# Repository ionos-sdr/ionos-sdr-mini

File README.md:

# Ionos SDR mini

Simplified, low-cost sibling of [Ionos SDR](https://github.com/ionos-sdr/ionos-sdr): a carrier PCB that turns a stock Silicon Labs radio board into a usable SDR. An ESP32-S3 DevKitC sits on female headers on the left, a Silicon Labs radio board plugs into the mezzanine socket on the right, and both displays are optional. No custom RF design, no exotic parts — the radio board you already have in a drawer does the RF.

*rev-B3, the 2-layer variant (signals on F.Cu and B.Cu, GND poured on both sides and stitched). KiCad 10 ray-traced render: DevKitC on headers, SSD1306 OLED with BACK/OK below it, the optional ER-TFTM024-3 TFT on a 2x20 socket in the middle (manufacturer's 3D model), cursor keys and the radio board connectors on the right. The render shows the shrouded Samtec TFC model; the JLC build uses the unshrouded TFM-120-02-L-D-K-TR on the same footprint.*

**Status: rev-B3 2L built and under test — ≈ 119 hours of measurements so far** ([report](docs/ionos-mini-measurements-2026-11.md)). The firmware lives in the [main repository](https://github.com/ionos-sdr/ionos-sdr); this repo holds the carrier board, its documentation and its measurements.

## What it is

- **Carrier only.** 168 x 80 mm, four M3 nylon standoffs. Two variants: 4-layer (`layout/rev-b3`, JLC04161H-7628: F.Cu GND / In1 signal / In2 GND + power / B.Cu signal) and this 2-layer one (`layout/rev-b3-2l`, 1.6 mm FR-4, GND pour and tracks on both layers; fit R1–R5 = 82 Ω here (twin_analog on the v2 routing; 22 Ω on the 4-layer board)). No RF layout risk: matching network, SMA and shielding stay on the Silicon Labs radio board.
- **Any radio board fits.** The mezzanine pair is the standard WSTK radio board interface, so BRD4265B (FG23, 434 MHz, 10 dBm) is only the first panel. The pin-to-signal mapping differs per panel and is selected in firmware.
- **Panel auto-detect.** The radio board's M24C02 board-ID EEPROM sits on the same I2C bus as the OLED, so the firmware can read which panel is plugged in and load the matching pin map at boot.
- **Bootstrap flashing.** SWDIO, SWCLK, SWO and RESET are routed to the ESP32, which bit-bangs SWD. A blank radio board can be programmed with nothing but this board and a USB cable; routine updates then go over the UART command link. For a J-Link or Simplicity Link there is also a 1x6 2.54 mm SWD footprint (CON3) on the right edge.
- **One cable.** Power and data over the DevKit's USB-C. The radio gets its own low-noise LDO from the 5 V rail, not the DevKit's shared 3.3 V.

## Architecture

- **RX**: FG23 I/Q capture and server-side FFT lines over SPI2 (IO_MUX) to the ESP32-S3, then to the host or to the on-board display.
- **Control**: RDY handshake and a UART command link; SWD is bit-banged by the ESP32 so a blank panel can be programmed with nothing but this board.
- **Power**: a single low-noise LDO feeds VMCU_IN; the radio board's own DC-DC handles PAVDD, so one supply pin powers the whole panel.

## Hardware

| Block | Part | Notes |
| --- | --- | --- |
| MCU | ESP32-S3-DevKitC-1, N16R8 | On 2x22 female headers, antenna end overhanging the board edge |
| Radio | Silicon Labs radio board | 2x 2x20, 1.27 mm mezzanine, 24 mm apart; BRD4265B validated first |
| Display (optional) | EastRising ER-TFTM024-3, 2.4", ILI9341 | 240x320, TE pin wired for tear-free hardware scroll; resistive or capacitive touch |
| Display (optional) | SSD1306 0.96" OLED, I2C | Status line when the large display is not fitted |
| Buttons | 6+1 tactile, C&K PTS647 | UP/DOWN/LEFT/RIGHT plus BACK/OK, a seventh SPARE footprint (key optional); two resistor ladders |
| Debug (optional) | 1x6 2.54 mm SWD footprint, CON3 | Not fitted; pogo clip or solder-in pins, see below |
| Radio supply | LP5907-3.3 or TPS7A2033 | ~6.5 uVrms, fed from the DevKit 5 V rail, ferrite + 10 uF at the connector |

Seven keys cost two pins, not seven: both ladders use the same 10 k pull-up and the same 0 R / 2.2 k / 6.8 k / 22 k set to GND (UP/DOWN/LEFT/RIGHT on GPIO2, BACK/OK/SPARE on GPIO1, the 22 k level of that ladder left free), read on ADC1 with a 1 k + 100 nF filter at the pin. One threshold table serves both: 0.30 / 0.97 / 1.80 / 2.79 V. Only the 0 R keys (UP, BACK) can wake the chip from deep sleep. The freed GPIOs carry the SWD lines.

## Pin mapping (BRD4265B)

The EXP header numbers come from the Silicon Labs radio board documentation; the connector pins are what you actually route. For EXP 3 to 16 the P201 pin number equals the EXP number.

| Signal | ESP32-S3 GPIO | FG23 pin | WSTK net | Connector pin |
| --- | --- | --- | --- | --- |
| SCLK | 12 (SPI2 IO_MUX) | PC05 | WSTK_P12 | P201-15 |
| MOSI | 11 (SPI2 IO_MUX) | PC00 | WSTK_P7 | P201-10 |
| CS | 10 (SPI2 IO_MUX) | PA07 | WSTK_P10 | P201-13 |
| RDY | 14 | PD02 | WSTK_P6 | P201-9 |
| CMD | 13 (UART TX) | PA06 | WSTK_P8 | P201-11 |
| SWDIO | 38 | PA02 | WSTK_P18 | P201-21 |
| SWCLK | 39 | PA01 | WSTK_P20 | P201-23 |
| SWO | 48 | PA03 | WSTK_P16 | P201-19 |
| RESETn | 40 | RESETn | WSTK_F4 | P200-17 |
| BOARD_ID_SDA / SCL | 41 / 42 (I2C0) | - | BOARD_ID | P200-40 / P200-39 |
| VMCU_IN | - | - | VMCU_IN | P201-2 |
| 3V3 | - | - | 3V3 | P200-1 |
| GND | - | - | GND | P200-2, 38; P201-1, 39 |

The FG23 link runs on SPI2 through the IO_MUX pins so the slave interface keeps its headroom for higher clocks; the optional TFT is on SPI3. `VRF` is unused on BRD4265B and the on-board DC-DC feeds PAVDD, so a single supply pin powers the whole panel; P201-40 (VRF_IN) only runs to test point TP8, and P200-37 (5 V) has a not-fitted 0 R (R33) from the DevKit 5 V for panels that need it.

## Display and touch

The ER-TFTM024-3 sits on SPI3 (SCK 4, MOSI 5, MISO 6, CS 7, D/C 15, RST 16, BL 17, TE 18). Its resistive touch controller (XPT2046) and the module's optional SD/font/flash chips share a second header bus (pins 32/33/34), which is tied to the TFT bus on the carrier; the touch transactions run at their own ~2 MHz clock. 10 k pull-ups hold the module's SD/FONT/FLASH chip selects (header 35/36/37) inactive so nothing else drives MISO.

| Pin | Resistive (XPT2046) | Capacitive (I2C CTP) |
| --- | --- | --- |
| TCH_A, GPIO8, header 30 | SPI CS | I2C SCL |
| TCH_B, GPIO21, header 31 | PENIRQ | I2C SDA |
| TCH_INT, GPIO9, header 39 | unused | CTP INT |

Both 4.7 k pull-ups (TCH_A, TCH_B) are fitted in every build, so one BOM serves both panel types; firmware picks the mode. **Before the first power-up**, measure the panel's MISO/TE high level with VDD = 5 V: if it follows 5 V, run the panel from 3V3 or add level shifting.

## DevKit: clone or official

The carrier is laid out for the AliExpress ESP32-S3 DevKit clone, whose RGB LED is on GPIO47. On official Espressif ESP32-S3-DevKitC-1 boards the WS2812 sits on GPIO38 (v1.1) or GPIO48 (v1.0), which are SWDIO and SWO here: with an official board the LED flickers during SWD and loads the line, so remove the LED or its series resistor, or use the clone.

## SWD debug header

CON3 is a 1x6 2.54 mm row of plated holes on the right edge, outside the radio board's outline, so it stays reachable with the radio board plugged in. Pin order follows the Tag-Connect TC2030-CTX:

| Pin | 1 | 2 | 3 | 4 | 5 | 6 |
| --- | --- | --- | --- | --- | --- | --- |
| Signal | VTref (VMCU) | SWDIO | nRESET | SWCLK | GND | SWO |

The pins connect on the radio side of the solder-jumper cut points. With a debugger attached, either keep the ESP32's SWD pins as inputs in firmware or cut JP2 and JP6-JP8 to detach the ESP32 completely. VTref only senses the radio board's VMCU; the debugger must not power the board through it.

## Measurements

**Time on test so far: ≈ 119 hours** (rev-B3 2L + BRD4265B, 2–13 Nov 2026; a weekend run continues until 16 Nov):
≈ 68 h RF with a signal generator (Signal Hound VSG60), ≈ 19 h RF without a source (self-noise, residual spurs, coverage), ≈ 32 h USB-only soaks.
Raw data, scripts, logs and charts: [`measurements/ionos-mini-2026-11/`](measurements/ionos-mini-2026-11/) ([RESULT.md](measurements/ionos-mini-2026-11/RESULT.md)) · report for 2–9 Nov: [`docs/ionos-mini-measurements-2026-11.md`](docs/ionos-mini-measurements-2026-11.md) ([magyarul](docs/hu/ionos-mini-meresi-jelentes-2026-11.md)).

**Measurement types:** USB throughput and long soaks · gain, linearity and ADC clip point · noise figure and MDS · passband and image rejection · frequency accuracy and drift · tuning range (LO divider / VCO window) · lock proof with the on-board clock comb · noise floor and residual spurs (open and terminated input) · 2-FSK sensitivity and BER curves · spurious responses 30 MHz – 6 GHz · long-term stability · SoapySDR driver soak. Pending: two-tone IIP3, phase noise, TX output vs frequency.

| BRD4265B (434 MHz match) | |
|---|---|
| Receive coverage | **97 – 1562 MHz and 2025 – 3100 MHz** (no LO divider for ~1625 – 2000 MHz) |
| 434 MHz (matched) | gain 63 dB, NF 3–4 dB, MDS −133 dBm (10 dB SNR, 500 Hz), 2-FSK 5 kbps BER 10⁻² at −115 dBm, clip −62 dBm |
| 145 MHz | gain 53 dB, NF 8–9 dB, MDS −128 dBm, FSK −110 dBm, clip −53 dBm |
| 868 / 1296 MHz | NF ≈ 23 / 40 dB, FSK −93 / −73 dBm |
| 2400 / 3000 MHz | NF ≈ 55 / 46 dB, FSK −55 / −59 dBm — the 434 MHz RX match limits above ~600 MHz, the chip itself tunes and locks to 3.1 GHz |
| Spurious responses | @ 434 MHz worst −70 dBc (11 × LO), others ≤ −104 dBc, no image response; @ 868 MHz worst −81 dBc |
| I/Q over USB (TinyUSB CDC on USB‑OTG) | 200 ksps int16 (813 kB/s); 40 h: 86 M blocks, 0 device drops, 0.65 ppm host loss |
| 200 ksps bandwidth / image rejection | 88 kHz at −3 dB (PHY channel filter) / ≥ 42 dB |
| Frequency | crystal ≈ +4.2…+5.3 ppm uncorrected (temperature), corrected in firmware (`FREQ_CORR_RX_PPB`); gain stable to σ 0.02–0.03 dB below 1 GHz |
| SoapySDR | SoapyIonos works on Windows (GQRX, SoapySDRUtil, Python); every VSG run goes through it |
| Known artefact | ±6.25 kHz sidebands (−74 dBc at 5 kHz, −43 dBc at 37 kHz tone offset) from the I/Q path — open |

P_in = VSG level − 30 dB pad; the coax loss is not subtracted (matters above ~1 GHz).

## Manufacturing files

Gerbers, drill, JLCPCB BOM and CPL are attached to the GitHub release [`rev-b3-2l-jlc-20261022`](https://github.com/ionos-sdr/ionos-sdr-mini/releases/tag/rev-b3-2l-jlc-20261022), not committed. To rebuild them from the KiCad project (DRC and schematic parity must be clean, or nothing is written):

```
"C:\Program Files\KiCad\10.0\bin\python.exe" fab/jlc_pack.py
```

JLC assembles the top-side SMD parts and the two radio board connectors; the DevKit, the displays and the debug header are fitted by hand. LCSC part numbers are in `fab/jlc_lcsc.csv`.

## Repository

```
hardware/          KiCad project, fab outputs, BOM           CERN-OHL-P-2.0
docs/              pin mapping, assembly notes, renders      CC-BY-4.0
measurements/      raw data, scripts, results                CC-BY-4.0
```

Firmware lives in the [main repository](https://github.com/ionos-sdr/ionos-sdr): `firmware-fg23/` for the radio SoC, `firmware-esp32/` for the companion.

## Credits, licensing, trademarks

Hardware under CERN-OHL-P-2.0, documentation under CC-BY-4.0. Not affiliated with IONOS SE or Silicon Laboratories; EFR32, Simplicity Studio and the WSTK radio board interface are Silicon Labs property, used here for interoperability only.

Designed by Zoltán Dóczi and Zoltán Papp at [Z2 Labs](https://www.z2labs.io/), Budapest. Design and manufacturing support by [Protowoerk](https://www.protowoerk.com).

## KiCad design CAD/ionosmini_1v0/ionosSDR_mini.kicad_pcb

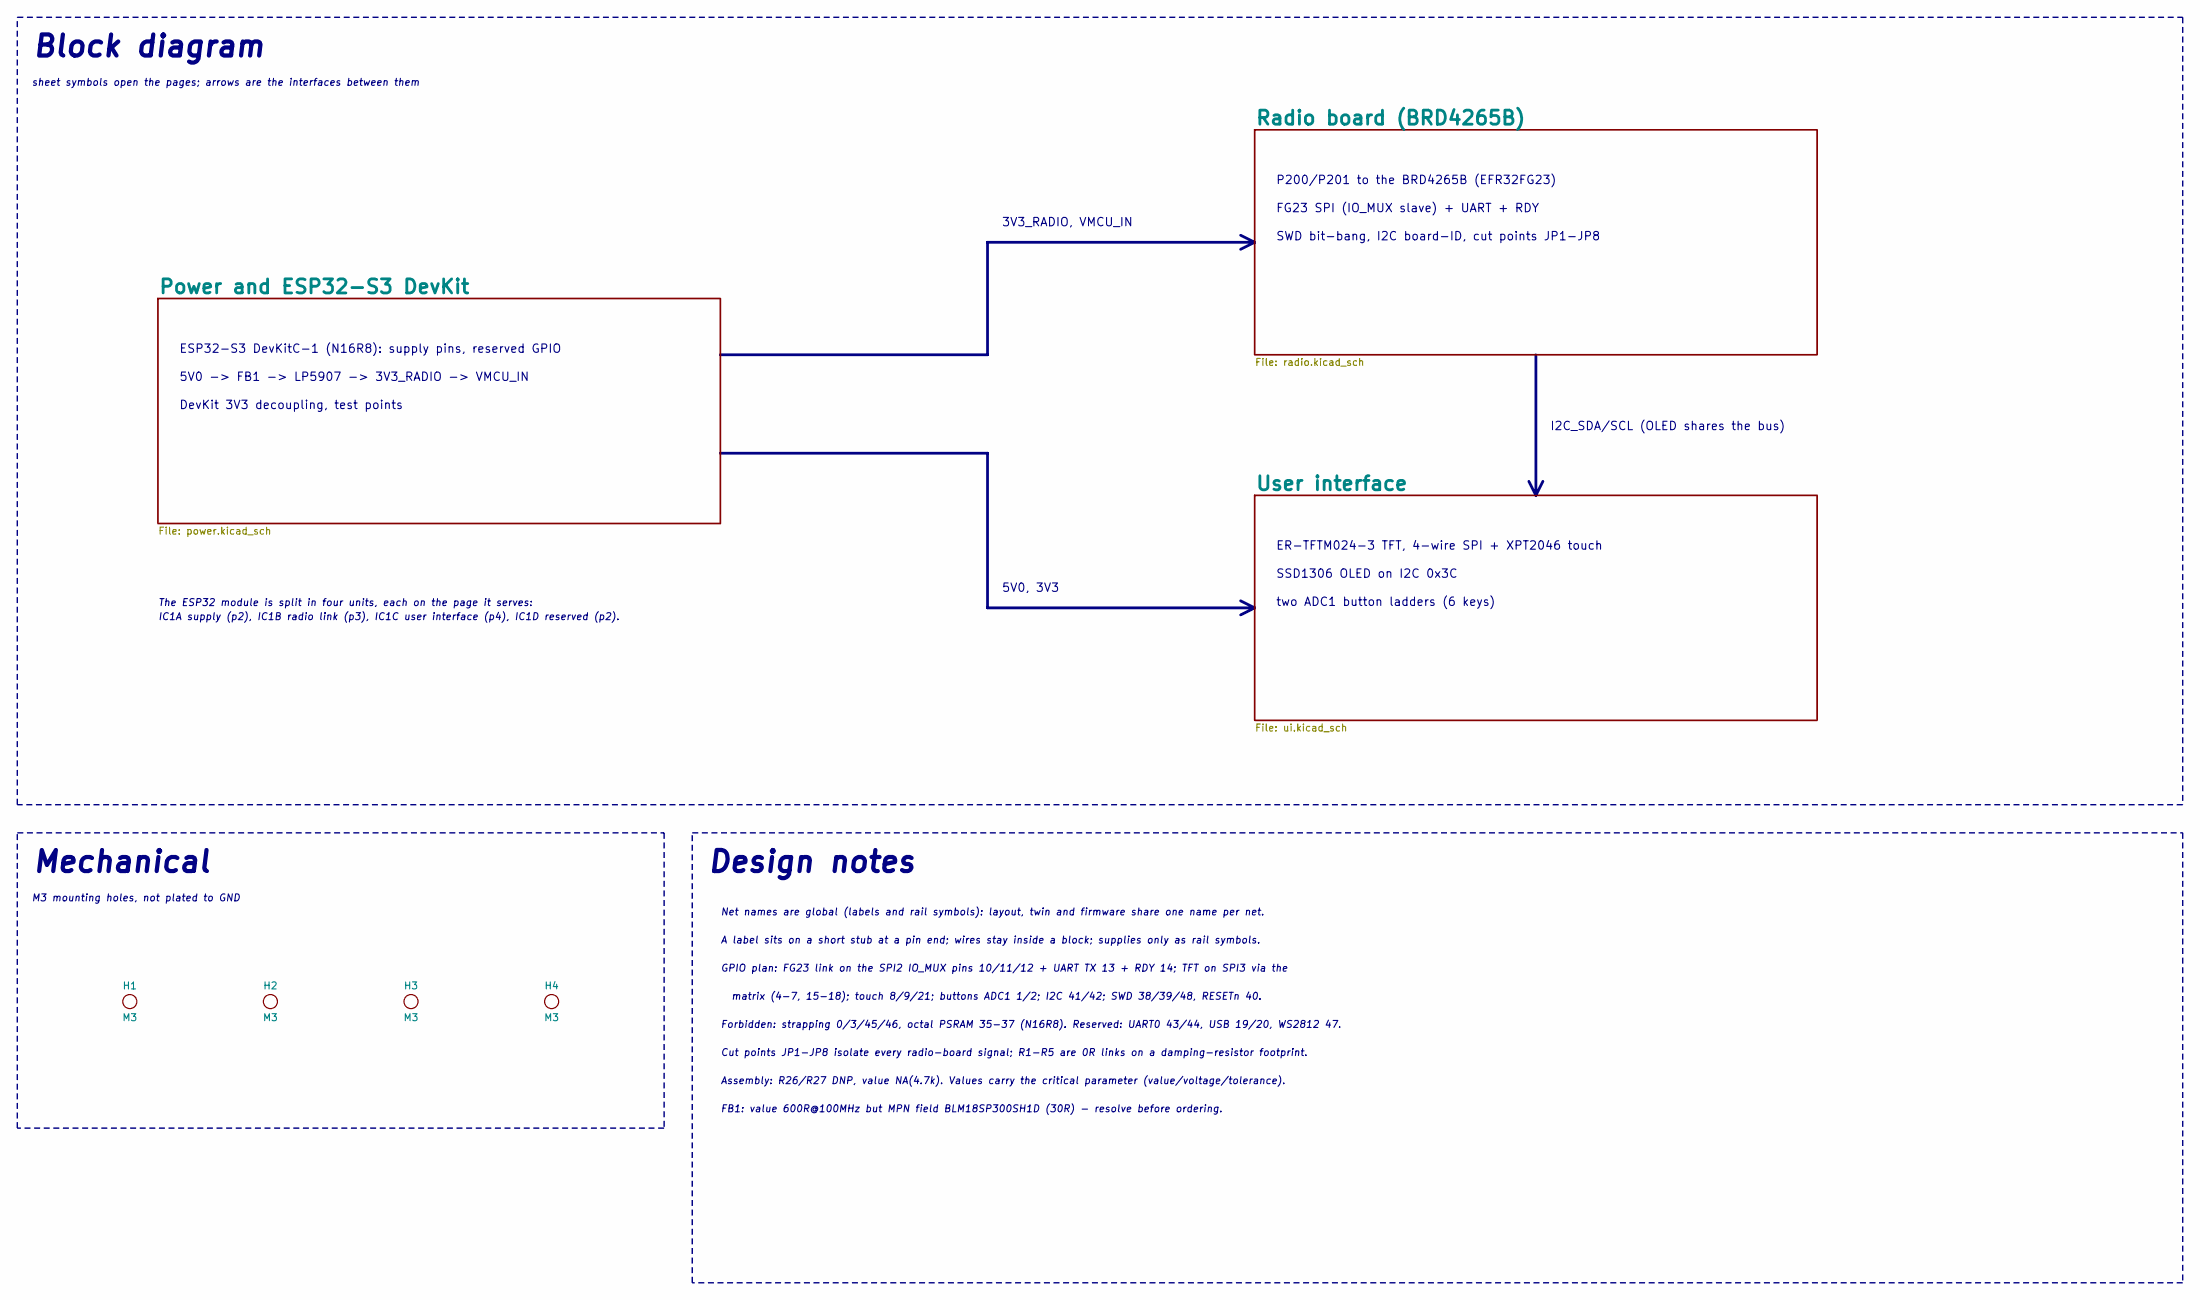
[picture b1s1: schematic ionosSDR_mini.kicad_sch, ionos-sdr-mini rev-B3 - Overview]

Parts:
H1, H2, H3, H4: M3; PB_HOLE

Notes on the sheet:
Block diagram
sheet symbols open the pages; arrows are the interfaces between them
ESP32-S3 DevKitC-1 (N16R8): supply pins, reserved GPIO
5V0 -> FB1 -> LP5907 -> 3V3_RADIO -> VMCU_IN
DevKit 3V3 decoupling, test points
P200/P201 to the BRD4265B (EFR32FG23)
FG23 SPI (IO_MUX slave) + UART + RDY
SWD bit-bang, I2C board-ID, cut points JP1-JP8
ER-TFTM024-3 TFT, 4-wire SPI + XPT2046 touch
SSD1306 OLED on I2C 0x3C
two ADC1 button ladders (6 keys)
3V3_RADIO, VMCU_IN
5V0, 3V3
I2C_SDA/SCL (OLED shares the bus)
The ESP32 module is split in four units, each on the page it serves:
IC1A supply (p2), IC1B radio link (p3), IC1C user interface (p4), IC1D reserved (p2).
Mechanical
M3 mounting holes, not plated to GND
Design notes
Net names are global (labels and rail symbols): layout, twin and firmware share one name per net.
A label sits on a short stub at a pin end; wires stay inside a block; supplies only as rail symbols.
GPIO plan: FG23 link on the SPI2 IO_MUX pins 10/11/12 + UART TX 13 + RDY 14; TFT on SPI3 via the
matrix (4-7, 15-18); touch 8/9/21; buttons ADC1 1/2; I2C 41/42; SWD 38/39/48, RESETn 40.
Forbidden: strapping 0/3/45/46, octal PSRAM 35-37 (N16R8). Reserved: UART0 43/44, USB 19/20, WS2812 47.
Cut points JP1-JP8 isolate every radio-board signal; R1-R5 are 0R links on a damping-resistor footprint.
Assembly: R26/R27 DNP, value NA(4.7k). Values carry the critical parameter (value/voltage/tolerance).
FB1: value 600R@100MHz but MPN field BLM18SP300SH1D (30R) - resolve before ordering.

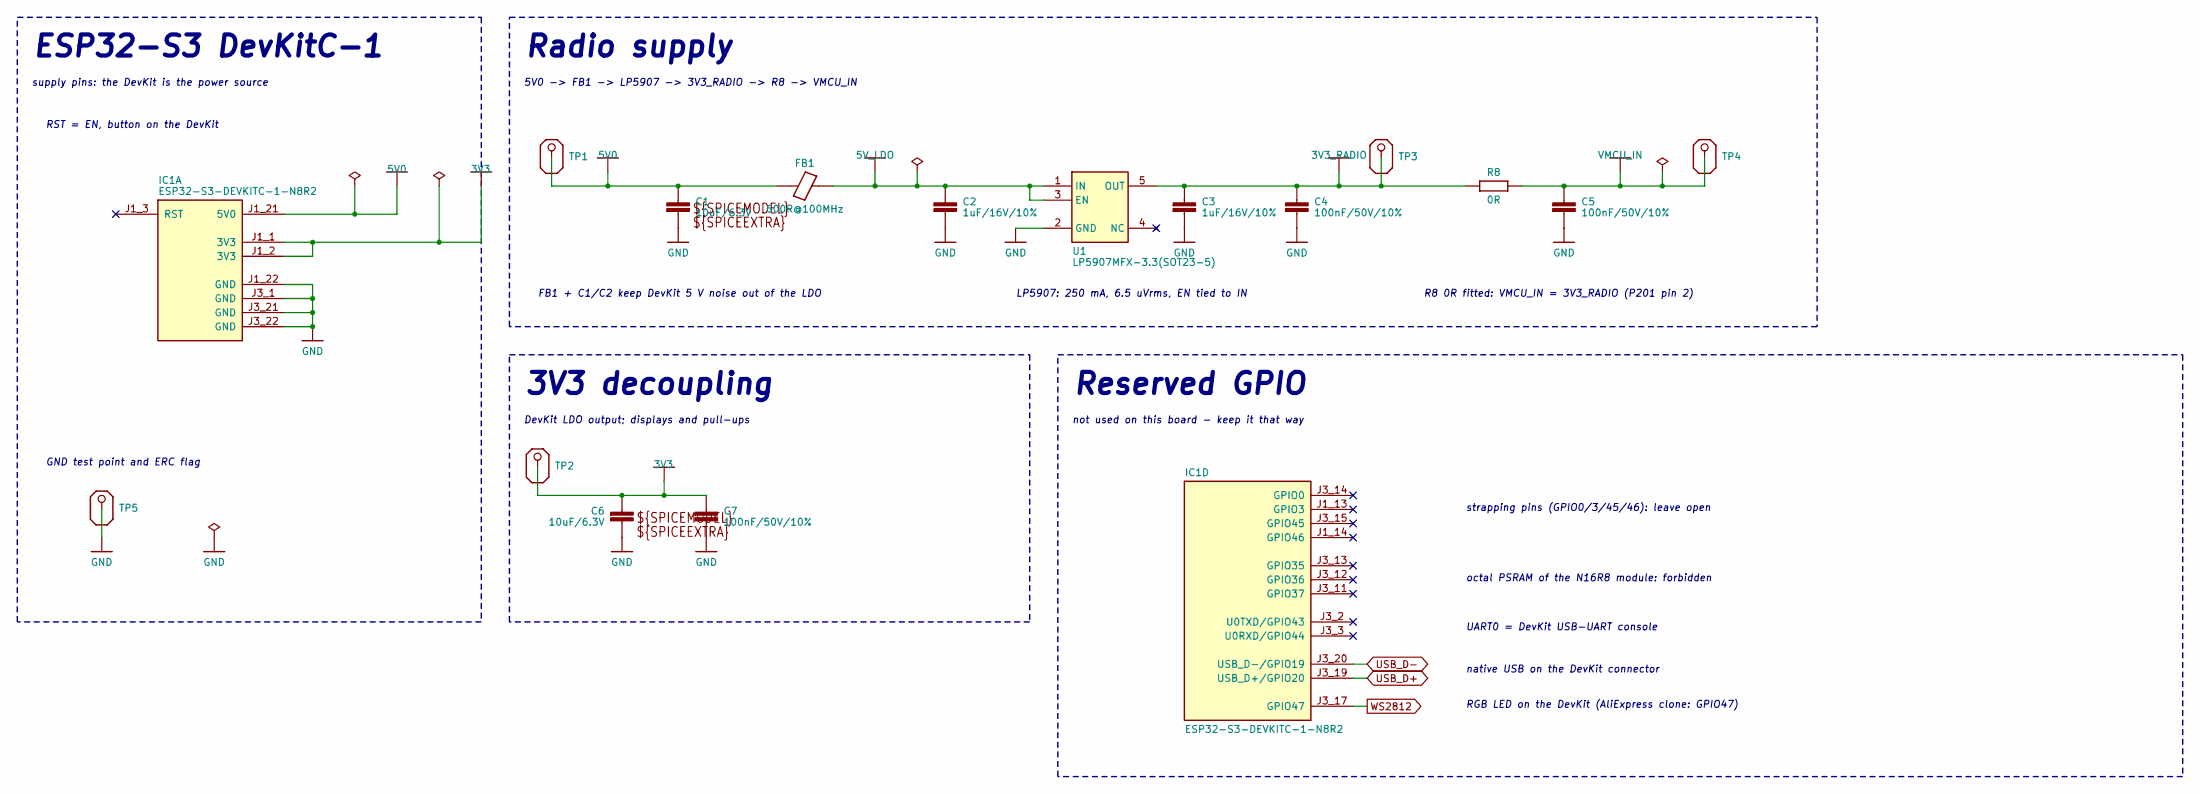
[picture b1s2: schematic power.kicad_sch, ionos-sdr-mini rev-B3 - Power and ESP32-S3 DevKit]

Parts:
C1, C6: 10uF/6.3V; CAPC1005X60_0402
C2, C3: 1uF/16V/10%; CAPC1005X60_0402; MPN CL05A105KO5NNNC
C4, C5, C7: 100nF/50V/10%; CAPC1005X60_0402; MPN GRM155R71H104KE14D
FB1: 600R@100MHz; L5_0603; MPN BLM18SP300SH1D
IC1: ESP32-S3-DEVKITC-1-N8R2; XCVR_ESP32-S3-DEVKITC-1-N8R2; MPN ESP32-S3-DEVKITC-1-N8R2
R8: 0R; RESC1005X40_0402; MPN CRCW04020000Z0EDC
TP1: 5V0; TESTPOINT_40MIL_SMD
TP2: 3V3; TESTPOINT_40MIL_SMD
TP3: 3V3_RADIO; TESTPOINT_40MIL_SMD
TP4: VMCU_IN; TESTPOINT_40MIL_SMD
TP5: GND; TESTPOINT_40MIL_SMD
U1: LP5907MFX-3.3(SOT23-5); SOT-23-5; MPN LP5907MFX-3.3/NOPB

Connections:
3V3: C6.1, C7.1, IC1.J1_1 (3V3), IC1.J1_2 (3V3), TP2.PP; also elsewhere on the board
3V3_RADIO: C3.1, C4.1, R8.1, TP3.PP, U1.5 (OUT); also elsewhere on the board
5V0: C1.1, FB1.1, IC1.J1_21 (5V0), TP1.PP; also elsewhere on the board
5V_LDO: C2.1, FB1.2, U1.1 (IN), U1.3 (EN)
GND: C1.2, C2.2, C3.2, C4.2, C5.2, C6.2, C7.2, IC1.J1_22 (GND), IC1.J3_1 (GND), IC1.J3_21 (GND), IC1.J3_22 (GND), TP5.PP, U1.2 (GND); also elsewhere on the board
USB_D+: IC1.J3_19 (USB_D+/GPIO20)
USB_D-: IC1.J3_20 (USB_D-/GPIO19)
VMCU_IN: C5.1, R8.2, TP4.PP; also elsewhere on the board
WS2812: IC1.J3_17 (GPIO47)

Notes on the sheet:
ESP32-S3 DevKitC-1
supply pins: the DevKit is the power source
GND test point and ERC flag
RST = EN, button on the DevKit
Radio supply
5V0 -> FB1 -> LP5907 -> 3V3_RADIO -> R8 -> VMCU_IN
FB1 + C1/C2 keep DevKit 5 V noise out of the LDO
LP5907: 250 mA, 6.5 uVrms, EN tied to IN
R8 0R fitted: VMCU_IN = 3V3_RADIO (P201 pin 2)
3V3 decoupling
DevKit LDO output; displays and pull-ups
Reserved GPIO
not used on this board - keep it that way
strapping pins (GPIO0/3/45/46): leave open
octal PSRAM of the N16R8 module: forbidden
UART0 = DevKit USB-UART console
native USB on the DevKit connector
RGB LED on the DevKit (AliExpress clone: GPIO47)

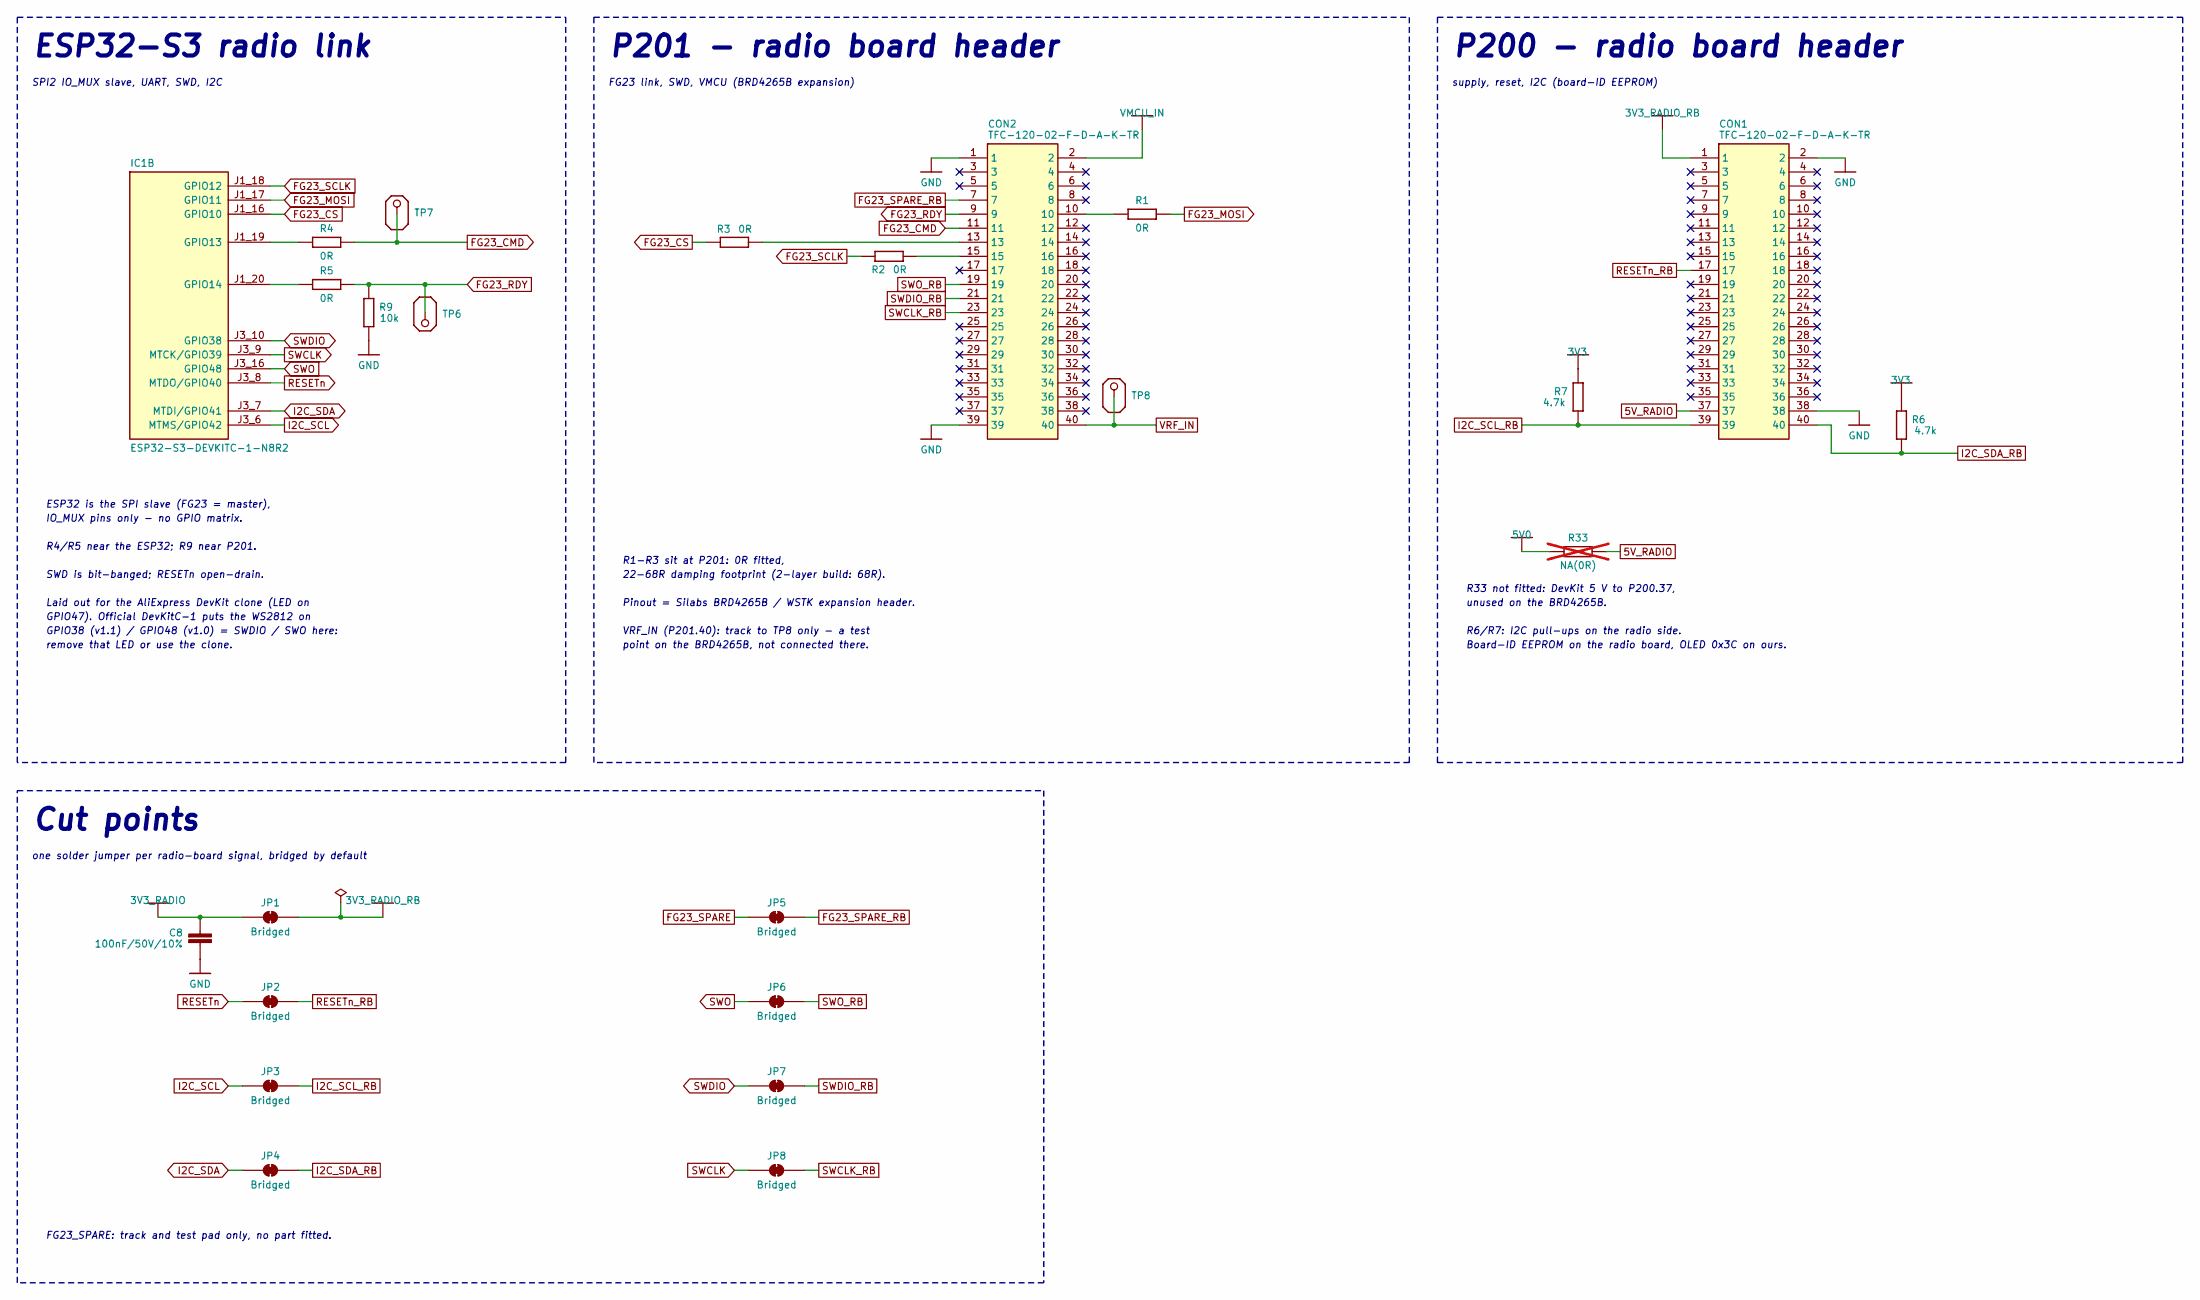
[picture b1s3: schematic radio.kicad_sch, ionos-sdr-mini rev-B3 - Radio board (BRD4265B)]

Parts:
C8: 100nF/50V/10%; CAPC1005X60_0402; MPN GRM155R71H104KE14D
CON1, CON2: TFC-120-02-F-D-A-K-TR; TFC-120-02-XX-D-A-K-TR; MPN TFC-120-02-F-D-A-K-TR
IC1: ESP32-S3-DEVKITC-1-N8R2; XCVR_ESP32-S3-DEVKITC-1-N8R2; MPN ESP32-S3-DEVKITC-1-N8R2
JP1, JP2, JP3, JP4, JP5, JP6, JP7, JP8: Bridged; SolderJumper-2_P1.3mm_Bridged_RoundedPad1.0x1.5mm
R1, R2, R3, R4, R5: 0R; RESC1005X40_0402; MPN CRCW04020000Z0EDC
R6, R7: 4.7k; RESC1005X40_0402; MPN CR0402AJW-472GAS
R9: 10k; RESC1005X40_0402; MPN CRCW040210K0FKED
R33: NA(0R); RESC1005X40_0402; MPN CRCW04020000Z0EDC; not fitted
TP6: FG23_RDY; TESTPOINT_40MIL_SMD
TP7: FG23_CMD; TESTPOINT_40MIL_SMD
TP8: VRF_IN; TESTPOINT_40MIL_SMD

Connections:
3V3: R6.2, R7.2; also elsewhere on the board
3V3_RADIO: C8.1, JP1.1 (A); also elsewhere on the board
3V3_RADIO_RB: CON1.1, JP1.2 (B)
5V0: R33.1; also elsewhere on the board
5V_RADIO: CON1.37, R33.2
FG23_CMD: CON2.11, R4.1, TP7.PP
FG23_CS: IC1.J1_16 (GPIO10), R3.1
FG23_MOSI: IC1.J1_17 (GPIO11), R1.2
FG23_RDY: CON2.9, R5.1, R9.1, TP6.PP
FG23_SCLK: IC1.J1_18 (GPIO12), R2.1
FG23_SPARE: JP5.1 (A)
FG23_SPARE_RB: CON2.7, JP5.2 (B)
GND: C8.2, CON1.2, CON1.38, CON2.1, CON2.39, R9.2; also elsewhere on the board
I2C_SCL: IC1.J3_6 (MTMS/GPIO42), JP3.1 (A); also elsewhere on the board
I2C_SCL_RB: CON1.39, JP3.2 (B), R7.1
I2C_SDA: IC1.J3_7 (MTDI/GPIO41), JP4.1 (A); also elsewhere on the board
I2C_SDA_RB: CON1.40, JP4.2 (B), R6.1
unnamed: CON2.10, R1.1
unnamed: CON2.13, R3.2
unnamed: CON2.15, R2.2
unnamed: IC1.J1_19 (GPIO13), R4.2
unnamed: IC1.J1_20 (GPIO14), R5.2
RESETn: IC1.J3_8 (MTDO/GPIO40), JP2.1 (A)
RESETn_RB: CON1.17, JP2.2 (B); also elsewhere on the board
SWCLK: IC1.J3_9 (MTCK/GPIO39), JP8.1 (A)
SWCLK_RB: CON2.23, JP8.2 (B); also elsewhere on the board
SWDIO: IC1.J3_10 (GPIO38), JP7.1 (A)
SWDIO_RB: CON2.21, JP7.2 (B); also elsewhere on the board
SWO: IC1.J3_16 (GPIO48), JP6.1 (A)
SWO_RB: CON2.19, JP6.2 (B); also elsewhere on the board
VMCU_IN: CON2.2; also elsewhere on the board
VRF_IN: CON2.40, TP8.PP

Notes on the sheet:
ESP32-S3 radio link
SPI2 IO_MUX slave, UART, SWD, I2C
ESP32 is the SPI slave (FG23 = master),
IO_MUX pins only - no GPIO matrix.
R4/R5 near the ESP32; R9 near P201.
SWD is bit-banged; RESETn open-drain.
Laid out for the AliExpress DevKit clone (LED on
GPIO47). Official DevKitC-1 puts the WS2812 on
GPIO38 (v1.1) / GPIO48 (v1.0) = SWDIO / SWO here:
remove that LED or use the clone.
P201 - radio board header
FG23 link, SWD, VMCU (BRD4265B expansion)
VRF_IN (P201.40): track to TP8 only - a test
point on the BRD4265B, not connected there.
R1-R3 sit at P201: 0R fitted,
22-68R damping footprint (2-layer build: 68R).
Pinout = Silabs BRD4265B / WSTK expansion header.
P200 - radio board header
supply, reset, I2C (board-ID EEPROM)
R33 not fitted: DevKit 5 V to P200.37,
unused on the BRD4265B.
R6/R7: I2C pull-ups on the radio side.
Board-ID EEPROM on the radio board, OLED 0x3C on ours.
Cut points
one solder jumper per radio-board signal, bridged by default
FG23_SPARE: track and test pad only, no part fitted.

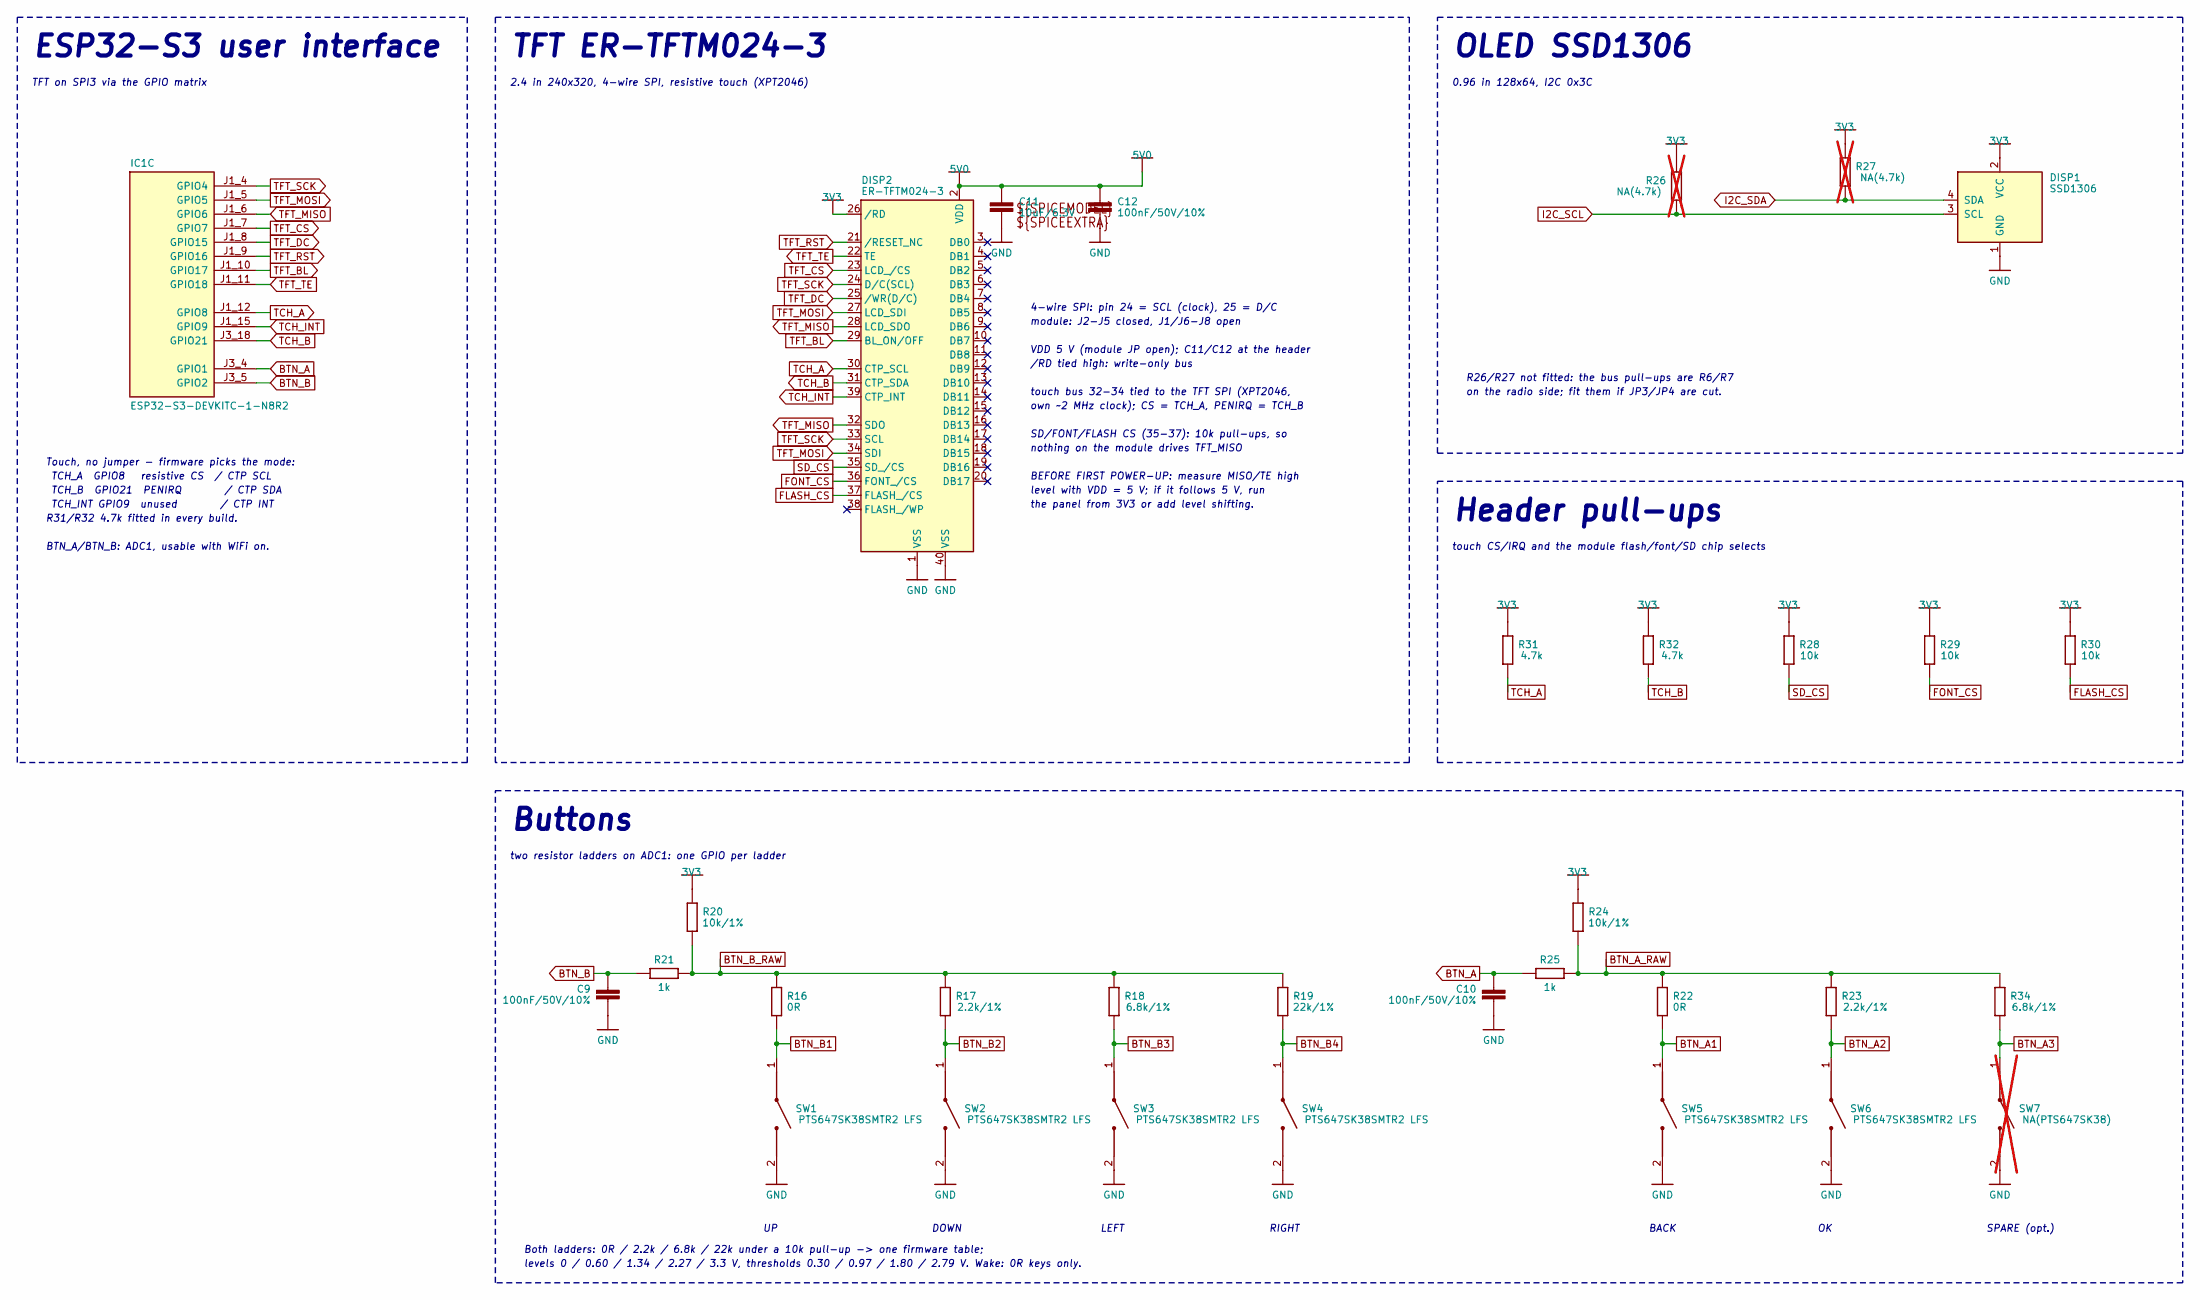
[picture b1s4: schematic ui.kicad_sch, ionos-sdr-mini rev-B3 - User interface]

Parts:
C9, C10, C12: 100nF/50V/10%; CAPC1005X60_0402; MPN GRM155R71H104KE14D
C11: 10uF/6.3V; CAPC1005X60_0402
DISP1: SSD1306; 128x64OLED; MPN OLED 4pin BLUE
DISP2: ER-TFTM024-3; ER-TFTM024-3_Socket_2x20_P2.54mm
IC1: ESP32-S3-DEVKITC-1-N8R2; XCVR_ESP32-S3-DEVKITC-1-N8R2; MPN ESP32-S3-DEVKITC-1-N8R2
R16, R22: 0R; RESC1005X40_0402; MPN CRCW04020000Z0EDC
R17, R23: 2.2k/1%; RESC1005X40_0402; MPN RT0402FRE072K2L
R18, R34: 6.8k/1%; RESC1005X40_0402; MPN RC0402FR-136K8L
R19: 22k/1%; RESC1005X70_0402; MPN ERA-2AED223X
R20, R24: 10k/1%; RESC1005X40_0402; MPN CRCW040210K0FKED
R21, R25: 1k; RESC1005X40_0402; MPN CR0402-FX-1001GLF
R26, R27: NA(4.7k); RESC1005X40_0402; MPN CR0402AJW-472GAS; not fitted
R28, R29, R30: 10k; RESC1005X40_0402; MPN CRCW040210K0FKED
R31, R32: 4.7k; RESC1005X40_0402; MPN CR0402AJW-472GAS
SW1, SW2, SW3, SW4, SW5, SW6: PTS647SK38SMTR2 LFS; PTS647SK38SMTR2LFS; MPN PTS647SK38SMTR2 LFS
SW7: NA(PTS647SK38); PTS647SK38SMTR2LFS; MPN PTS647SK38SMTR2 LFS; not fitted

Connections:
3V3: DISP1.2 (VCC), DISP2.26 (/RD), R20.1, R24.1, R26.1, R27.1, R28.1, R29.1, R30.1, R31.1, R32.1; also elsewhere on the board
5V0: C11.1, C12.1, DISP2.2 (VDD); also elsewhere on the board
BTN_A: C10.1, IC1.J3_4 (GPIO1), R25.2
BTN_A1: R22.2, SW5.1
BTN_A2: R23.2, SW6.1
BTN_A3: R34.2, SW7.1
BTN_A_RAW: R22.1, R23.1, R24.2, R25.1, R34.1
BTN_B: C9.1, IC1.J3_5 (GPIO2), R21.2
BTN_B1: R16.2, SW1.1
BTN_B2: R17.2, SW2.1
BTN_B3: R18.2, SW3.1
BTN_B4: R19.2, SW4.1
BTN_B_RAW: R16.1, R17.1, R18.1, R19.1, R20.2, R21.1
FLASH_CS: DISP2.37 (FLASH_/CS), R30.2
FONT_CS: DISP2.36 (FONT_/CS), R29.2
GND: C9.2, C10.2, C11.2, C12.2, DISP1.1 (GND), DISP2.1 (VSS), DISP2.40 (VSS), SW1.2, SW2.2, SW3.2, SW4.2, SW5.2, SW6.2, SW7.2; also elsewhere on the board
I2C_SCL: DISP1.3 (SCL), R26.2; also elsewhere on the board
I2C_SDA: DISP1.4 (SDA), R27.2; also elsewhere on the board
SD_CS: DISP2.35 (SD_/CS), R28.2
TCH_A: DISP2.30 (CTP_SCL), IC1.J1_12 (GPIO8), R31.2
TCH_B: DISP2.31 (CTP_SDA), IC1.J3_18 (GPIO21), R32.2
TCH_INT: DISP2.39 (CTP_INT), IC1.J1_15 (GPIO9)
TFT_BL: DISP2.29 (BL_ON/OFF), IC1.J1_10 (GPIO17)
TFT_CS: DISP2.23 (LCD_/CS), IC1.J1_7 (GPIO7)
TFT_DC: DISP2.25 (/WR(D/C)), IC1.J1_8 (GPIO15)
TFT_MISO: DISP2.28 (LCD_SDO), DISP2.32 (SDO), IC1.J1_6 (GPIO6)
TFT_MOSI: DISP2.27 (LCD_SDI), DISP2.34 (SDI), IC1.J1_5 (GPIO5)
TFT_RST: DISP2.21 (/RESET_NC), IC1.J1_9 (GPIO16)
TFT_SCK: DISP2.24 (D/C(SCL)), DISP2.33 (SCL), IC1.J1_4 (GPIO4)
TFT_TE: DISP2.22 (TE), IC1.J1_11 (GPIO18)

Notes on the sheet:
ESP32-S3 user interface
TFT on SPI3 via the GPIO matrix
Touch, no jumper - firmware picks the mode:
TCH_A GPIO8 resistive CS / CTP SCL
TCH_B GPIO21 PENIRQ / CTP SDA
TCH_INT GPIO9 unused / CTP INT
R31/R32 4.7k fitted in every build.
BTN_A/BTN_B: ADC1, usable with WiFi on.
TFT ER-TFTM024-3
2.4 in 240x320, 4-wire SPI, resistive touch (XPT2046)
4-wire SPI: pin 24 = SCL (clock), 25 = D/C
module: J2-J5 closed, J1/J6-J8 open
VDD 5 V (module JP open); C11/C12 at the header
/RD tied high: write-only bus
touch bus 32-34 tied to the TFT SPI (XPT2046,
own ~2 MHz clock); CS = TCH_A, PENIRQ = TCH_B
SD/FONT/FLASH CS (35-37): 10k pull-ups, so
nothing on the module drives TFT_MISO
BEFORE FIRST POWER-UP: measure MISO/TE high
level with VDD = 5 V; if it follows 5 V, run
the panel from 3V3 or add level shifting.
OLED SSD1306
0.96 in 128x64, I2C 0x3C
R26/R27 not fitted: the bus pull-ups are R6/R7
on the radio side; fit them if JP3/JP4 are cut.
Header pull-ups
touch CS/IRQ and the module flash/font/SD chip selects
Buttons
two resistor ladders on ADC1: one GPIO per ladder
DOWN
LEFT
RIGHT
BACK
SPARE (opt.)
Both ladders: 0R / 2.2k / 6.8k / 22k under a 10k pull-up -> one firmware table;
levels 0 / 0.60 / 1.34 / 2.27 / 3.3 V, thresholds 0.30 / 0.97 / 1.80 / 2.79 V. Wake: 0R keys only.

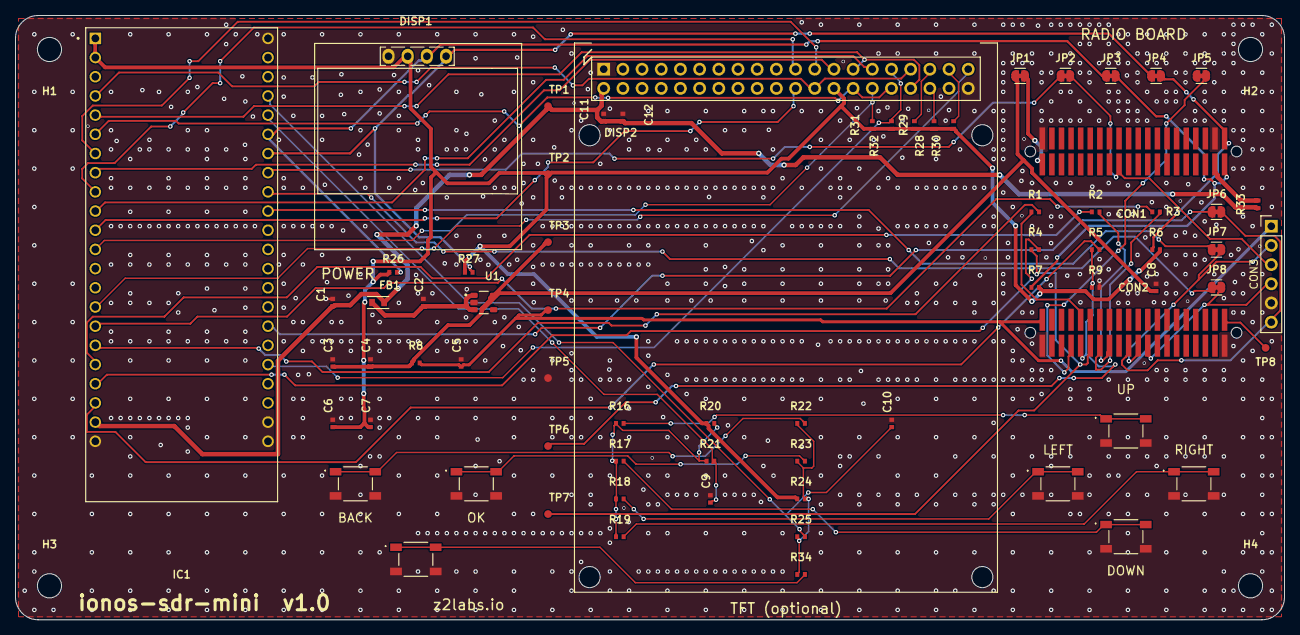
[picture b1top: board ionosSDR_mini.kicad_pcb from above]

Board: 2 copper layers, 168.0 x 80.0 mm, 75 parts (0 on the bottom side), 57 nets.

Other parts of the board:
CON3: NA(SWD 1x6 2.54); PinHeader_1x06_P2.54mm_Vertical

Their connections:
GND: CON3.5; also elsewhere on the board
RESETn_RB: CON3.3; also elsewhere on the board
SWCLK_RB: CON3.4; also elsewhere on the board
SWDIO_RB: CON3.2; also elsewhere on the board
SWO_RB: CON3.6; also elsewhere on the board
VMCU_IN: CON3.1; also elsewhere on the board

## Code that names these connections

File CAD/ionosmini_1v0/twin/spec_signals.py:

# -*- coding: utf-8 -*-
"""Independent machine-readable specification of the ionos-sdr-mini wiring.

Written from the SOURCE DOCUMENTS, not from the schematic:

  * BRD4265B-A01 schematic, sheet 4 (P200 / P201 pin tables)
  * BRD4265B-A01 BOM and drill file (connector type and alignment pins)
  * ESP32-S3-WROOM-1 N16R8 datasheet (pin restrictions)
  * ER-TFTM024-3 datasheet section 4.1 (header pin assignment)

The checker compares the exported netlist against this.  If the two ever
disagree, one of them is wrong - and that is the whole point.
"""

# ---------------------------------------------------------------- mezzanine
# Verified on the Silabs sheet: P201 carries WSTK_P0..P35 on pins 3..38, so
# WSTK_Pn sits on P201 pin n+3.  P200 carries WSTK_F0..F21 on pins 13..34,
# so WSTK_Fn sits on P200 pin n+13.
def p201_pin(wstk_p):
    return wstk_p + 3


def p200_pin(wstk_f):
    return wstk_f + 13


CON_OF = {"P200": "CON1", "P201": "CON2"}

MEZZ_FIXED = {
    ("P200", 1): "3V3", ("P200", 2): "GND",
    ("P200", 35): "5V", ("P200", 36): "USB_VREG", ("P200", 37): "USB_VBUS",
    ("P200", 38): "GND",
    ("P200", 39): "BOARD_ID_SCL", ("P200", 40): "BOARD_ID_SDA",
    ("P201", 1): "GND", ("P201", 2): "VMCU_IN",
    ("P201", 39): "GND", ("P201", 40): "NC",
}

# ------------------------------------------------------------------ signals
# net, ESP32 header pin, (connector, pin), direction, domain
SIGNALS = [
    ("FG23_SCLK",  "J1_18", ("CON2", p201_pin(12)), "in",    "3V3"),
    ("FG23_MOSI",  "J1_17", ("CON2", p201_pin(7)),  "in",    "3V3"),
    ("FG23_CS",    "J1_16", ("CON2", p201_pin(10)), "in",    "3V3"),
    ("FG23_CMD",   "J1_19", ("CON2", p201_pin(8)),  "out",   "3V3"),
    # RDY is an ESP32 OUTPUT: the ESP32 is the SPI slave and has to arm its
    # DMA before the FG23 may clock the next block out.  See
    # claude/FG23-kijelzopanel-valasztas-2026-08-17.md ("RDY (ki)", "CMD (ki)").
    ("FG23_RDY",   "J1_20", ("CON2", p201_pin(6)),  "out",   "3V3"),
    ("FG23_SPARE", None,    ("CON2", p201_pin(4)),  "spare", "3V3"),
    ("SWDIO",      "J3_10", ("CON2", p201_pin(18)), "bidir", "3V3"),
    ("SWCLK",      "J3_9",  ("CON2", p201_pin(20)), "out",   "3V3"),
    ("SWO",        "J3_16", ("CON2", p201_pin(16)), "in",    "3V3"),
    ("RESETn",     "J3_8",  ("CON1", p200_pin(4)),  "out",   "3V3"),
    ("I2C_SDA",    "J3_7",  ("CON1", 40), "bidir", "3V3"),
    ("I2C_SCL",    "J3_6",  ("CON1", 39), "out",   "3V3"),
    ("3V3_RADIO",  None,    ("CON1", 1),  "power", "3V3"),
    ("VMCU_IN",    None,    ("CON2", 2),  "power", "3V3"),
]

# every signal leaving at the socket needs exactly one cut point
CUT_POINTS = {
    "FG23_SCLK": "R2", "FG23_MOSI": "R1", "FG23_CS": "R3",
    "FG23_CMD": "R4", "FG23_RDY": "R5", "VMCU_IN": "R8",
    "3V3_RADIO": "JP1", "RESETn": "JP2", "I2C_SCL": "JP3",
    "I2C_SDA": "JP4", "FG23_SPARE": "JP5", "SWO": "JP6",
    "SWDIO": "JP7", "SWCLK": "JP8",
}

# ---------------------------------------------------- ESP32-S3 pin rules
ESP_GPIO = {
    "J1_1": "3V3", "J1_2": "3V3", "J1_3": "RST",
    "J1_4": 4, "J1_5": 5, "J1_6": 6, "J1_7": 7, "J1_8": 15, "J1_9": 16,
    "J1_10": 17, "J1_11": 18, "J1_12": 8, "J1_13": 3, "J1_14": 46,
    "J1_15": 9, "J1_16": 10, "J1_17": 11, "J1_18": 12, "J1_19": 13,
    "J1_20": 14, "J1_21": "5V0", "J1_22": "GND",
    "J3_1": "GND", "J3_2": 43, "J3_3": 44, "J3_4": 1, "J3_5": 2,
    "J3_6": 42, "J3_7": 41, "J3_8": 40, "J3_9": 39, "J3_10": 38,
    "J3_11": 37, "J3_12": 36, "J3_13": 35, "J3_14": 0, "J3_15": 45,
    "J3_16": 48, "J3_17": 47, "J3_18": 21, "J3_19": 20, "J3_20": 19,
    "J3_21": "GND", "J3_22": "GND",
}

FORBIDDEN = {
    33: "octal PSRAM (N16R8)", 34: "octal PSRAM (N16R8)",
    35: "octal PSRAM (N16R8)", 36: "octal PSRAM (N16R8)",
    37: "octal PSRAM (N16R8)",
    26: "SPI flash", 27: "SPI flash", 28: "SPI flash", 29: "SPI flash",
    30: "SPI flash", 31: "SPI flash", 32: "SPI flash",
    19: "native USB D-", 20: "native USB D+",
}

STRAPPING = {
    0: "BOOT, must be high at reset",
    3: "JTAG source select",
    45: "VDD_SPI voltage select, must be low at reset",
    46: "ROM message printing, must be low at reset",
}

IOMUX_FSPI = {10: "FSPICS0", 11: "FSPID", 12: "FSPICLK",
              13: "FSPIQ", 14: "FSPIWP"}

ADC1 = {1: "ADC1_CH0", 2: "ADC1_CH1", 3: "ADC1_CH2", 4: "ADC1_CH3",
        5: "ADC1_CH4", 6: "ADC1_CH5", 7: "ADC1_CH6", 8: "ADC1_CH7",
        9: "ADC1_CH8", 10: "ADC1_CH9"}

# ------------------------------------------------------- display (DISP2)
TFT = {
    1: ("VSS", "GND"), 2: ("VDD", "5V0"), 40: ("VSS", "GND"),
    21: ("RESET", "TFT_RST"), 22: ("TE", "TFT_TE"),
    23: ("LCD_CS", "TFT_CS"), 24: ("SCL", "TFT_SCK"),
    25: ("D/C", "TFT_DC"), 26: ("RD", "3V3"),
    27: ("LCD_SDI", "TFT_MOSI"), 28: ("LCD_SDO", "TFT_MISO"),
    29: ("BL_ON", "TFT_BL"),
    30: ("RTP_CS / CTP_SCL", "TCH_A"),
    31: ("RTP_PEN / CTP_SDA", "TCH_B"),
    32: ("SDO aux", "TFT_MISO"), 33: ("SCL aux", "TFT_SCK"),
    34: ("SDI aux", "TFT_MOSI"),
    35: ("SD_CS", "SD_CS"), 36: ("FONT_CS", "FONT_CS"), 37: ("FLASH_CS", "FLASH_CS"),
    39: ("FLASH_HOLD / CTP_INT", "TCH_INT"),
}

# ---------------------------------------------------------- button ladders
# node, ADC pin, pull-up, series filter R, filter C, [(switch, R to GND)]
LADDERS = [
    ("BTN_B", "J3_5", 10000.0, 1000.0, 100e-9,
     [("SW1", 0.0), ("SW2", 2200.0), ("SW3", 6800.0), ("SW4", 22000.0)]),
    ("BTN_A", "J3_4", 10000.0, 1000.0, 100e-9,
     [("SW5", 0.0), ("SW6", 2200.0), ("SW7", 6800.0)]),
]

# ---------------------------------------------------------- pin map v2 (2026-10-09)
# Source: claude/ionos-mini-pinmap-v2-2026-10-09.md (Google Sheet pin map v2,
# decisions D1-D5 and section 8).  Each line is checked against the netlist by
# twin_check.check_pinmap_v2(), so a later edit cannot quietly undo it.
TOUCH_GPIO = {            # D1: TCH_B = GPIO21, TCH_INT = GPIO9
    "TCH_A": "J1_12",     # GPIO8
    "TCH_B": "J3_18",     # GPIO21
    "TCH_INT": "J1_15",   # GPIO9
}
# (net, part, ohms, other side): pull-ups that must exist and be fitted
PULLUPS = [
    ("TCH_A", "R31", 4700.0, "3V3"),      # section 6: fit in every build
    ("TCH_B", "R32", 4700.0, "3V3"),
    ("SD_CS", "R28", 10000.0, "3V3"),     # D2: module chips share SPI3
    ("FONT_CS", "R29", 10000.0, "3V3"),
    ("FLASH_CS", "R30", 10000.0, "3V3"),
]
# (connector, pin, net, part on the net, that part's other net, fitted?)
MEZZ_V2 = [
    ("CON1", 37, "5V_RADIO", "R33", "5V0", False),   # unfitted 0R to DevKit 5 V
    ("CON2", 40, "VRF_IN", "TP8", None, True),       # track to a test point only
]
TFT_DECOUPLING = [("C11", "5V0"), ("C12", "5V0")]    # 10 uF + 100 nF at the header
# section 8: both ladders the same set (one firmware table); part per key in the netlist
LADDER_PARTS = {
    "BTN_A": [("SW5", "R22", 0.0), ("SW6", "R23", 2200.0), ("SW7", "R34", 6800.0)],
    "BTN_B": [("SW1", "R16", 0.0), ("SW2", "R17", 2200.0), ("SW3", "R18", 6800.0), ("SW4", "R19", 22000.0)],
}
# SWD debug header (2026-10-17): 1x6 2.54 mm footprint, not fitted, on the RADIO side of
# the cut points so an external debugger reaches the FG23 even with JP2/JP6-JP8 cut.
# Pin order = Tag-Connect TC2030-CTX. (pin, net, radio-board pin that net must reach)
SWD_HEADER = [
    (1, "VMCU_IN",   ("CON2", 2)),     # VTref: senses VMCU, never powers it
    (2, "SWDIO_RB",  ("CON2", 21)),
    (3, "RESETn_RB", ("CON1", 17)),
    (4, "SWCLK_RB",  ("CON2", 23)),
    (5, "GND",       ("CON2", 1)),
    (6, "SWO_RB",    ("CON2", 19)),
]
OPTIONAL_PARTS = {"SW7"}   # footprint fitted, key optional (DNP)
VDD_LADDER = 3.3
ADC_FS = 3.1          # ESP32-S3 ADC full scale with 12 dB attenuation
